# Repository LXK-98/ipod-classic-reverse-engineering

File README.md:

# iPod Classic (6G/7G) LCD — reverse-engineered pinout and protocol

Complete pinout, bus protocol and electrical characterisation of the 2.5" 320×240 LCD
in the **iPod Classic 2009 "thin" 160 GB** (model A1238, logic board 820‑2437‑A,
Samsung S5L8702 — the revision Rockbox calls `ipod6g`).

Everything here was **measured**, not inferred from documentation. Where the results
disagree with the Rockbox source they are marked as such, with the evidence.

**Status:** all six original goals complete, the panel's initialisation sequence is verified
write-by-write on the bus (152/152), and **power sequencing is measured in both directions**
— the analog domain leads the logic domain by 218 ms coming up, and the order reverses
exactly going down. Remaining loose ends are in
[docs/OPEN-QUESTIONS.md](docs/OPEN-QUESTIONS.md); the one that still blocks a driver *board*
is the RGB666 pair test ([DRIVING.md §4](docs/DRIVING.md#4-pixel-format)).

---

## Results at a glance

| property | value |
|---|---|
| Flex connector | **34 pins**, 0.3 mm pitch |
| Panel variant | **type 2** (of Apple's four) — ILI9320/9326-style 16-bit register command set |
| Logic level | **1.8 V** |
| Bus | 8080-series parallel, **18-bit RGB666**, data latched on **rising edge of /WR** |
| Write cycle | **610 ns** (1.64 MHz) — 70–80 ns low, 530–540 ns high |
| Command writes | two regimes: **818 ns** (60–80 ns low) and **309 ns** (30–40 ns low) — both accepted by the panel |
| Full frame | 76 800 writes ≈ **46.9 ms** at 610 ns, **one transfer per pixel** |
| Measured pixel burst | **23.44–23.48 ms** — either half the panel at 610 ns or all of it at ~305 ns; the envelope cannot tell them apart |
| Init sequence | **146 writes**, 240 ms of sleeps — **all 152 wake writes verified byte-exact on the bus** |
| **Power-up order** | **3.0 V → 1.54 V reference (+0.13 ms) → 1.8 V VDDIO (+218.3 ms)** — reproduced 3× across 3 boot methods |
| **Power-down order** | **the exact mirror** — VDDIO → reference (+32.9 ms) → 3.0 V (+46.5 ms) |
| First LCD write | **+397.4 ms after VDDIO**; TE starts 12.5 ms after the init block |
| Refresh (TE) | **67.9 Hz** — measured 67.89–67.92 Hz, period 14.7227 ms, pulse 57–58 µs |
| Backlight | **4 white LEDs**, **19.5 mA**, **12.76 V** at full brightness, low-side PWM |

**[→ Full pinout: PINOUT.md](PINOUT.md)** (generated from [`pinout.json`](pinout.json))

*End-to-end proof: rows 0–3 of a live screen, reconstructed from a raw logic-analyzer
capture — blue icon, text glyphs, and the battery outline with its red low-charge fill.*

### Pin summary

| pins | function |
|---|---|
| 1, 2, 9–16, 18–25 | 18-lane RGB666 data bus |
| 3, 6, 8, 17, 31 | GND |
| 4, 5 | Backlight anode (**12.76 V ⚠️**) / cathode via 25.6 Ω sense |
| 7 | TE (tearing effect, 67.9 Hz) |
| 26, 33 | VDDIO 1.8 V / 3.0 V rail |
| 27, 28, 29 | /WR, D/C, /CS |
| 30, 32 | /RD and /RESET — both active-low, idle high ([which is which: open](docs/OPEN-QUESTIONS.md)) |
| 34 | ~1.54 V analog reference — an **input** the panel expects |

> ⚠️ **Pin 4 reaches 12.76 V.** Never connect it to a logic analyzer — a TXU0104
> level shifter is rated 5.5 V absolute maximum on its input side.

---

## Documentation

| document | contents |
|---|---|
| [PINOUT.md](PINOUT.md) | the pinout table, generated from `pinout.json` |
| **[docs/DRIVING.md](docs/DRIVING.md)** | **how to build a driver — start here for Phase 6** |
| [docs/BREADBOARD.md](docs/BREADBOARD.md) | the RP2040 breadboard driver: wiring, firmware, bring-up milestones, pair test |
| [docs/HARDWARE.md](docs/HARDWARE.md) | target device, interposer, instrumentation, safety rules |
| [docs/PROTOCOL.md](docs/PROTOCOL.md) | bus protocol, init sequences, timing, pixel format |
| [docs/METHODOLOGY.md](docs/METHODOLOGY.md) | how each result was obtained and how to reproduce it |
| [docs/FINDINGS.md](docs/FINDINGS.md) | notable findings, including where reality differs from the Rockbox source |
| [docs/OPEN-QUESTIONS.md](docs/OPEN-QUESTIONS.md) | what is still unresolved |
| [docs/LAB-NOTEBOOK.md](docs/LAB-NOTEBOOK.md) | the full chronological log, wrong turns included |

---

## Repository layout

```
PINOUT.md              generated pinout reference
pinout.json            single source of truth — everything else derives from this
docs/                  documentation (above) + the ModemManager udev rule
tools/                 capture, decode and reporting tools (Python, re-runnable)
firmware/              MicroPython breadboard driver for an RP2040 Pico (docs/BREADBOARD.md)
refs/                  Rockbox sources used as ground truth (GPL v2, see refs/README.md)
captures/              every logic-analyzer capture, gzipped, with JSON sidecars
measurements/          DMM sweeps as TSV
probe_maps/            probe wiring conventions
hardware/interposer/   KiCad project for the 34-pin passive interposer board
```

## Quick start

```bash
pip install -r requirements.txt

python3 tools/rockbox_seq.py --summary      # parse Rockbox into sequence tables
python3 tools/report.py                     # regenerate PINOUT.md from pinout.json
python3 tools/index_captures.py             # regenerate captures/INDEX.md

# decode any capture against the known lane map
python3 tools/decode8080.py captures/20260801_215011_dryrun.csv

# check a capture against the expected Rockbox sequence, write by write
python3 tools/seqmatch.py captures/20260803_203836_init-burst.csv

# reconstruct an image from a captured frame
python3 tools/frame2png.py captures/20260801_222433_dryrun.csv -o frame.png
```

Capturing new data needs the [gusmanb LogicAnalyzer](https://github.com/gusmanb/logicanalyzer)
binaries in `vendor/` (gitignored — download from that project's Releases).

---

## Headline findings

Three results contradict or resolve things the Rockbox source leaves open. Details and
evidence in [docs/FINDINGS.md](docs/FINDINGS.md).

1. **All 18 lanes are actively driven — none is idle.** Every lane is observed both high
   and low across solid-colour fills. `lcd-s5l8702.c` describes frame mode as
   `APB[15:0] -> D[17:10, 8:1]`, which would leave two lanes carrying nothing; a lane that
   is never driven cannot track colour data in both directions, and none behaves that way.
   The lanes group as **6 per colour channel (RGB666)**, and the data is consistent with
   the SoC expanding 5-bit channels by `6bit = (5bit << 1) | (5bit >> 4)`.
   *Caveat: that Rockbox comment block is headed `XXX: WIP, TBC` — its authors flagged it
   as unconfirmed, and their driver is correct regardless, since nothing in it depends on
   the comment.*
2. **Two pin pairs carry identical data under Rockbox** — pins 9/14 and 21/2 — consistent
   with each being the replicated MSB of a 5-bit channel widened to 6. They measure
   6.66 MΩ apart, so this is not a short. **Untested:** whether a driver can give those
   pairs *different* values for true 6-bit colour. All our data comes from an RGB565
   source, where they are identical by construction.
3. **One bus transfer per pixel**, confirmed by a 46.92 ms measured frame time matching
   76 800 × 610 ns to 0.1 %.

## Safety

- **Pin 4 (backlight anode) reaches 12.76 V** — destroys 5.5 V-rated shifter inputs
- Panel logic is **1.8 V**; a level shifter referenced to 3.3 V will *not* read it
  reliably (TXU0104 V<sub>T+</sub> max is 1.92 V at a 3 V reference, above a 1.8 V logic high)
- Ground instruments to **signal** ground (any of pins 3/6/8/17/31), not the chassis —
  the iPod bonds chassis to signal ground through **~300 Ω**
- Disconnect the battery before continuity testing; "powered off" still leaves PMU
  standby rails live

## Licensing

**This project is MIT licensed** — see [LICENSE](LICENSE). That covers the tools,
documentation, measurements, captures, `pinout.json` and the interposer hardware design.

**One exception:** the vendored Rockbox sources in [`refs/`](refs/) are **GPL v2** and are
redistributed under those terms, with the licence text at [`refs/COPYING`](refs/COPYING)
and provenance in [`refs/README.md`](refs/README.md). `refs/sequences.json` is generated
from them and is treated as a derived work under the same terms.

These sit alongside the project as separate works — GPL v2 §2 "mere aggregation" — so they
do not place the rest of the repository under the GPL. Nothing outside `refs/` contains
Rockbox code; `tools/rockbox_seq.py` only parses those files.

## Credits

Built on prior work by the [Rockbox](https://www.rockbox.org/) and
[freemyipod](https://freemyipod.org/) projects, whose driver source made byte-exact
validation possible. Capture hardware and firmware:
[gusmanb/logicanalyzer](https://github.com/gusmanb/logicanalyzer).

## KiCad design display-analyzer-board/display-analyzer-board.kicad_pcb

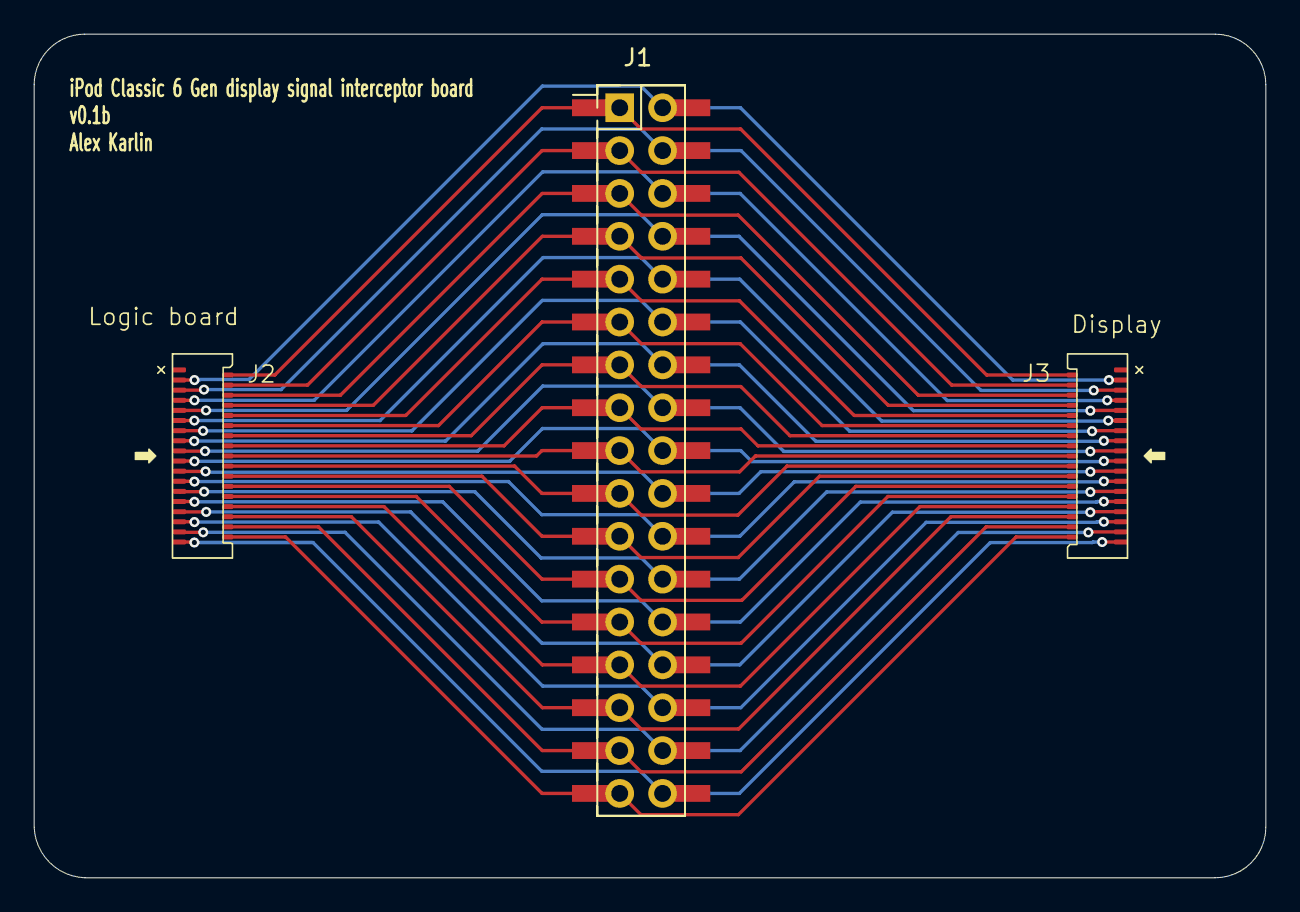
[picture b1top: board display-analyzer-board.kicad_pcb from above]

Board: 2 copper layers, 73.0 x 50.0 mm, 4 parts (0 on the bottom side), 34 nets.

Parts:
J1: Conn_02x17_Odd_Even; PinHeader_2x17_P2.54mm_Vertical_SMD
J2, J3: 046293635005829+
J4: Conn_02x17_Odd_Even; PinHeader_2x17_P2.54mm_Vertical

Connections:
/2: J1.1, J2.2, J3.34, J4.1
/3: J1.2, J2.3, J3.33, J4.2
/4: J1.3, J2.4, J3.32, J4.3
/5: J1.4, J2.5, J3.31, J4.4
/6: J1.5, J2.6, J3.30, J4.5
/7: J1.6, J2.7, J3.29, J4.6
/8: J1.7, J2.8, J3.28, J4.7
/9: J1.8, J2.9, J3.27, J4.8
/10: J1.9, J2.10, J3.26, J4.9
/11: J1.10, J2.11, J3.25, J4.10
/12: J1.11, J2.12, J3.24, J4.11
/13: J1.12, J2.13, J3.23, J4.12
/14: J1.13, J2.14, J3.22, J4.13
/15: J1.14, J2.15, J3.21, J4.14
/16: J1.15, J2.16, J3.20, J4.15
/17: J1.16, J2.17, J3.19, J4.16
/18: J1.17, J2.18, J3.18, J4.17
/19: J1.18, J2.19, J3.17, J4.18
/20: J1.19, J2.20, J3.16, J4.19
/21: J1.20, J2.21, J3.15, J4.20
/22: J1.21, J2.22, J3.14, J4.21
/23: J1.22, J2.23, J3.13, J4.22
/24: J1.23, J2.24, J3.12, J4.23
/25: J1.24, J2.25, J3.11, J4.24
/26: J1.25, J2.26, J3.10, J4.25
/27: J1.26, J2.27, J3.9, J4.26
/28: J1.27, J2.28, J3.8, J4.27
/29: J1.28, J2.29, J3.7, J4.28
/30: J1.29, J2.30, J3.6, J4.29
/31: J1.30, J2.31, J3.5, J4.30
/32: J1.31, J2.32, J3.4, J4.31
/33: J1.32, J2.33, J3.3, J4.32
/34: J1.33, J2.34, J3.2, J4.33
/35: J1.34, J2.35, J3.1, J4.34
